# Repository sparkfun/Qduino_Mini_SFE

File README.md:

Qduino Mini
========================================

[*Qduino Mini - Arduino Dev Board (DEV-13614)*](https://www.sparkfun.com/products/13614)

The Qduino Mini is *perfect* to embed in your electronics projects, it's super small, inexpensive, has a battery connector & charger built-in, & a fuel gauge that can tell you when to charge the battery!

The **Qduino Mini is Arduino-compatible & 100% open source, hardware and software** meaning that making and programming your first circuit is a breeze.  Hardware is hard, so we decided to make it a little bit easier.  All of the design files, including EAGLE board files, schematic, and code have been released under an open source license.  Here's what it includes:

* **Battery Charger Circuit** - just plug in USB and it charges the battery with the auto switching circuit - there's no extra charger needed & no digging the battery out of your project so you can charge & program at the same time over USB!
* **Battery Fuel Gauge** - guessing on when your project runs out of juice?  We've got you covered - we have a simple monitor library for your battery so you can remind yourself when it needs a little extra juice.
* **Ultra small, Ultra thin, Ultra light** - The Qduino Mini itself is 0.8in x 1.5in (2cm x 3.9cm) & 0.18oz (5 grams), perfect for quadcopters, drones or high altitude balloon projects.  Both the Qduino Mini and the batteries (LiPos) used to power the board fit are super compact & thin, just right for embedding in your projects.

<h4>Tech Specs:</h4>

* **ATmega32U4 Processor** - Arduino Leonardo Compatible
* 32KB Flash Storage
* 2.5KB SRAM
* 1KB EEPROM
* 3.3V @ 8MHz
* 20 Digital I/O // 14 Dedicated
* 12 Analog Channels // 6 Dedicated
* 7 Digital I/O also PWM channels
* SPI, I2C, UART available
* Two RGB LEDs built-in - one for: Charge Status, TX, RX, and the * other user programmable
* **TPS78233** 3.3V 150mA Regulator
* **MCP73832** LiPo Battery Charger
* **MAX17048** LiPo Battery Fuel Gauge

The Qduino Mini is 100% made in the USA! Every board is made and quality tested at SparkFun Electronics, in Niwot, CO.

Documentation
--------------
* **[Introducing the Qduino Mini!](https://www.sparkfun.com/news/1754)** 
* **[Hookup Guide](https://www.hackster.io/team-qtechknow/qduino-mini-quickstart-guide-8b2d68)** - Basic hookup guide
* **[Hackster.io: Projects](https://www.hackster.io/qtechknow)** - Projects using the Qduino.
* **SparkFun: Projects**
  * **[DIY Light Sculpture](https://learn.sparkfun.com/tutorials/diy-light-sculpture)**
  * **[DIY Light-Up Shoes](https://learn.sparkfun.com/tutorials/diy-light-up-shoes)**
* **[SparkFun Arduino Board Add-on](https://github.com/sparkfun/Arduino_Boards)** - Board Add-on for the Qduino Mini
* **[SparkFun Fritzing Part](https://github.com/sparkfun/Fritzing_Parts/blob/main/products/13614_sfe_qtechknow_qduino_mini_arduino_development_board.fzpz)** - Fritzing diagrams for SparkFun products.
* **[SparkFun Graphical Datasheets](https://github.com/sparkfun/Graphical_Datasheets/tree/master/Datasheets/Qduino)** - Graphical Datasheets for various SparkFun products.

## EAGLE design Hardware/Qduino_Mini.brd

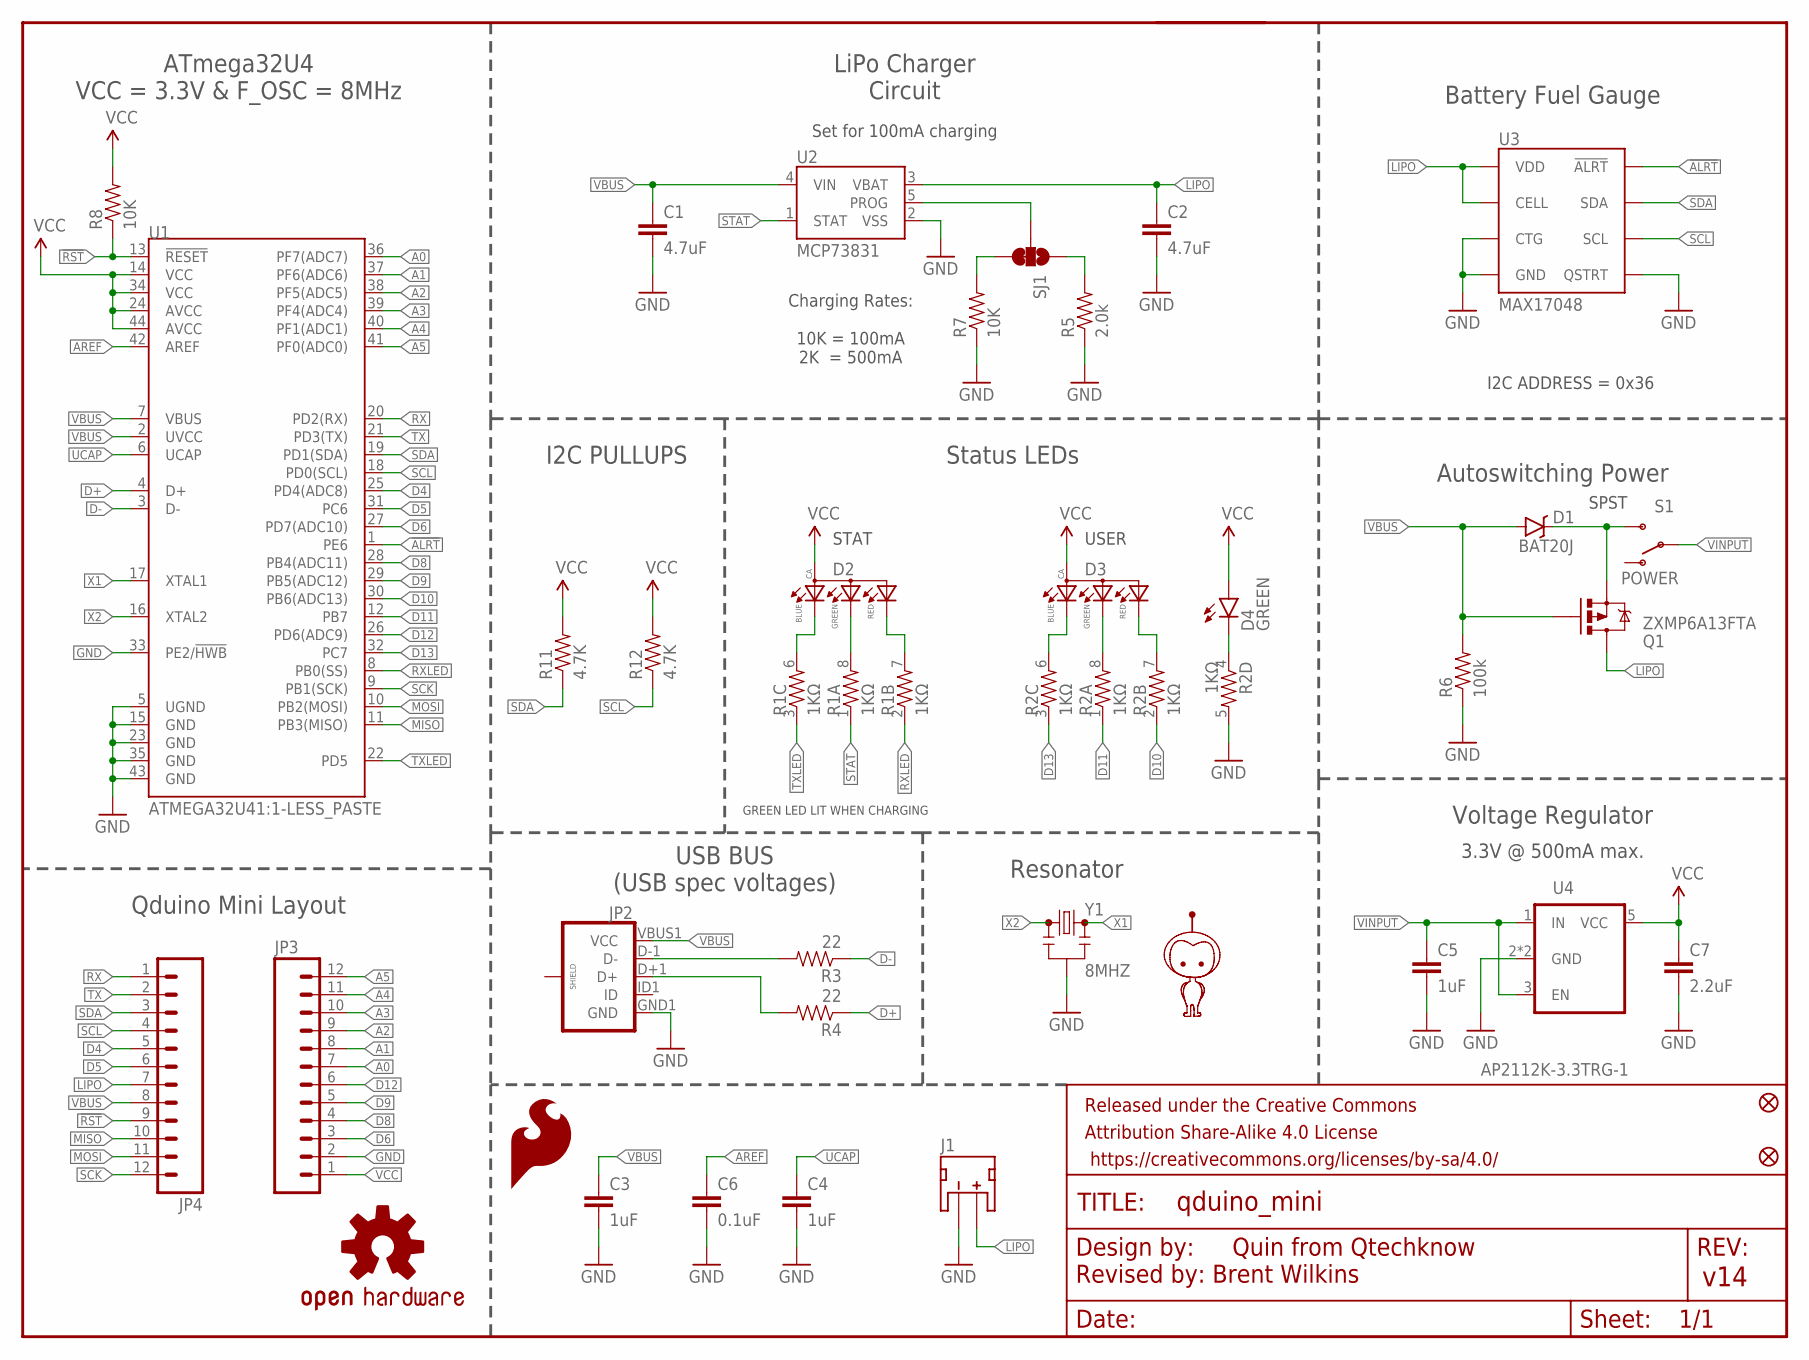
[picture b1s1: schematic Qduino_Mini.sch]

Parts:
C1, C2: 4.7uF; 0603-CAP
C3, C4, C5: 1uF; 0603-CAP
C6: 0.1uF; 0603-CAP
C7: 2.2uF; 0603-CAP
D1: BAT20J; SOD-323
D2, D3: 0.13_RGB_LEDPLCC; P-LCC-4-3
D4: GREEN; LED-0603
FID1, FID2: FIDUCIALUFIDUCIAL; MICRO-FIDUCIAL
FRAME2: FRAME-LETTER; CREATIVE_COMMONS
J1: LiPo; JST-2-SMD
JP2: USB_MICROB_PLUGCONN-11752; USB-B-MICRO-SMD_V03
JP3, JP4: M12PTH; 1X12
LOGO1: OSHW-LOGOS; OSHW-LOGO-S
LOGO2: SFE_LOGO_FLAME.1_INCH; SFE_LOGO_FLAME_.1
Q1: ZXMP6A13FTA; SOT23-3
R1, R2: 1KΩ; 0603-ARV
R3, R4: 22; 0603-RES
R5: 2.0k; 0603-RES
R6: 100k; 0603-RES
R7, R8: 10K; 0603-RES
R11, R12: 4.7K; 0603-RES
S1: POWER; SWITCH-SPST-SMD-A
SJ1: JUMPER-PAD-3-2OF3_NC_BY_TRACE_SMALL; PAD-JUMPER-3-2OF3_NC_BY_TRACE_YES_SILK_FULL_BOX
U1: ATMEGA32U41:1-LESS_PASTE; QFN-44-NOPAD_1:1-LESS_PASTE
U2: MCP73831; SOT23-5
U3: MAX17048; DFN-8
U4: AP2112K-3.3TRG-1; SOT23-5
U5: MIGHTYQ-L-SILK; LOGO-LARGE-SILK
Y1: 8MHZ; RESONATOR-SMD

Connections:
!ALRT: U1.1 (PE6), U3.P$5 (!ALRT)
!RST: JP4.9, R8.1, U1.13 (!RESET)
A0: JP3.7, U1.36 (PF7(ADC7))
A1: JP3.8, U1.37 (PF6(ADC6))
A2: JP3.9, U1.38 (PF5(ADC5))
A3: JP3.10, U1.39 (PF4(ADC4))
A4: JP3.11, U1.40 (PF1(ADC1))
A5: JP3.12, U1.41 (PF0(ADC0))
AREF: C6.1, U1.42 (AREF)
D4: JP4.5, U1.25 (PD4(ADC8))
D5: JP4.6, U1.31 (PC6)
D6: JP3.3, U1.27 (PD7(ADC10))
D8: JP3.4, U1.28 (PB4(ADC11))
D9: JP3.5, U1.29 (PB5(ADC12))
D10: R2.2 (1), U1.30 (PB6(ADC13))
D11: R2.1, U1.12 (PB7)
D12: JP3.6, U1.26 (PD6(ADC9))
D13: R2.3 (1), U1.32 (PC7)
D+: R4.1, U1.4 (D+)
D-: R3.1, U1.3 (D-)
GND: C1.2, C2.2, C3.2, C4.2, C5.2, C6.2, C7.2, J1.1 (-), JP2.GND1 (GND), JP3.2, R2.5 (2), R5.1, R6.1, R7.1, U1.5 (UGND), U1.15 (GND), U1.23 (GND), U1.33 (PE2/!HWB), U1.35 (GND), U1.43 (GND), U2.2 (VSS), U3.P$1 (CTG), U3.P$4 (GND), U3.P$6 (QSTRT), U3.P$9 (GND), U4.2 (GND), U4.4 (GND), Y1.2
INMOSFET: D1.C, Q1.2 (S), S1.3 (S)
LIPO: C2.1, J1.2 (+), JP4.7, Q1.3 (D), U2.3 (VBAT), U3.P$2 (CELL), U3.P$3 (VDD)
MISO: JP4.10, U1.11 (PB3(MISO))
MOSI: JP4.11, U1.10 (PB2(MOSI))
unnamed: D2.3 (BLUE), R1.6 (2)
unnamed: D2.2 (GREEN), R1.8 (2)
unnamed: D3.3 (BLUE), R2.6 (2)
unnamed: D4.C, R2.4 (1)
unnamed: R7.2, SJ1.3
unnamed: R5.2, SJ1.1
unnamed: D3.2 (GREEN), R2.8 (2)
unnamed: D2.1 (RED), R1.7 (2)
unnamed: D3.1 (RED), R2.7 (2)
PROG: SJ1.2, U2.5 (PROG)
RX: JP4.1, U1.20 (PD2(RX))
RXLED: R1.2 (1), U1.8 (PB0(SS))
SCK: JP4.12, U1.9 (PB1(SCK))
SCL: JP4.4, R12.1, U1.18 (PD0(SCL)), U3.P$7 (SCL)
SDA: JP4.3, R11.1, U1.19 (PD1(SDA)), U3.P$8 (SDA)
STAT: R1.1, U2.1 (STAT)
TX: JP4.2, U1.21 (PD3(TX))
TXLED: R1.3 (1), U1.22 (PD5)
UCAP: C4.1, U1.6 (UCAP)
UD+: JP2.D+1 (D+), R4.2
UD-: JP2.D-1 (D-), R3.2
VBUS: C1.1, C3.1, D1.A, JP2.VBUS1 (VCC), JP4.8, Q1.1 (G), R6.2, U1.2 (UVCC), U1.7 (VBUS), U2.4 (VIN)
VCC: C7.1, D2.4 (ANODE), D3.4 (ANODE), D4.A, JP3.1, R8.2, R11.2, R12.2, U1.14 (VCC), U1.24 (AVCC), U1.34 (VCC), U1.44 (AVCC), U4.5 (VCC)
VINPUT: C5.1, S1.2, U4.1 (IN), U4.3 (EN)
X1: U1.17 (XTAL1), Y1.3
X2: U1.16 (XTAL2), Y1.1

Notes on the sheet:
Set for 100mA charging
USB BUS (USB spec voltages)
Resonator
Status LEDs
3.3V @ 500mA max.
SPST
ATmega32U4 VCC = 3.3V & F_OSC = 8MHz
Qduino Mini Layout
LiPo Charger Circuit
Battery Fuel Gauge
Voltage Regulator
Autoswitching Power
Charging Rates: 10K = 100mA 2K = 500mA
I2C PULLUPS
Revised by: Brent Wilkins
I2C ADDRESS = 0x36
USER
STAT
GREEN LED LIT WHEN CHARGING

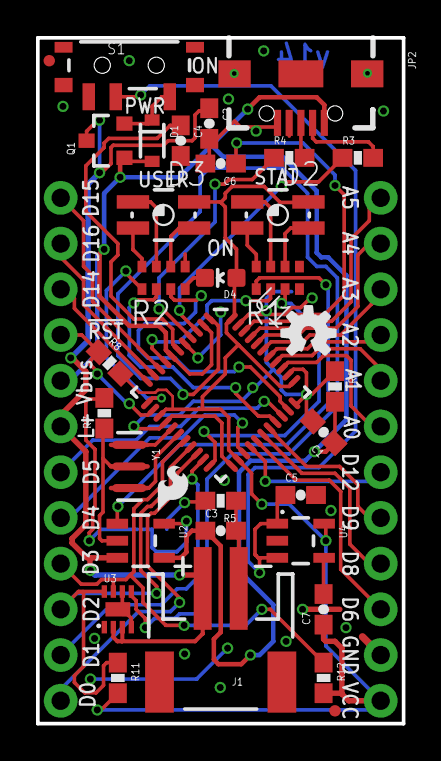
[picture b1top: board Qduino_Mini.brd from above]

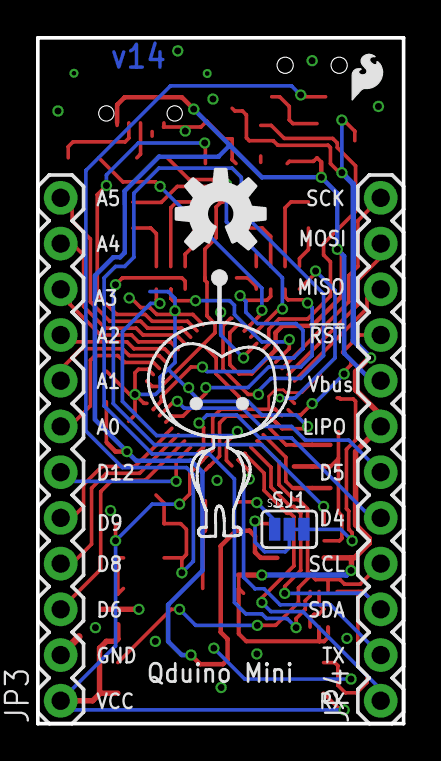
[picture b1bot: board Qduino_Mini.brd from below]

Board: 2 copper layers, 20.3 x 38.1 mm, 41 parts (6 on the bottom side), 51 nets.

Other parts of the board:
LOGO3: SFE_LOGO_FLAME.1_INCH; SFE_LOGO_FLAME_.1@1
U$4: OSHW-LOGO-M@1

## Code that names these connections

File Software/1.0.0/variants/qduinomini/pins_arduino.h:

/*
  pins_arduino.h - Pin definition functions for Arduino
  Part of Arduino - http://www.arduino.cc/

  Copyright (c) 2007 David A. Mellis

  This library is free software; you can redistribute it and/or
  modify it under the terms of the GNU Lesser General Public
  License as published by the Free Software Foundation; either
  version 2.1 of the License, or (at your option) any later version.

  This library is distributed in the hope that it will be useful,
  but WITHOUT ANY WARRANTY; without even the implied warranty of
  MERCHANTABILITY or FITNESS FOR A PARTICULAR PURPOSE.  See the GNU
  Lesser General Public License for more details.

  You should have received a copy of the GNU Lesser General
  Public License along with this library; if not, write to the
  Free Software Foundation, Inc., 59 Temple Place, Suite 330,
  Boston, MA  02111-1307  USA

  $Id: wiring.h 249 2007-02-03 16:52:51Z mellis $
*/

#ifndef Pins_Arduino_h
#define Pins_Arduino_h

#include <avr/pgmspace.h>

#define TX_RX_LED_INIT	DDRD |= (1<<5), DDRB |= (1<<0)
#define TXLED0			PORTD |= (1<<5)
#define TXLED1			PORTD &= ~(1<<5)
#define RXLED0			PORTB |= (1<<0)
#define RXLED1			PORTB &= ~(1<<0)

static const uint8_t SDA = 2;
static const uint8_t SCL = 3;

// Map SPI port to 'new' pins D14..D17
static const uint8_t SS   = 17;
static const uint8_t MOSI = 16;
static const uint8_t MISO = 14;
static const uint8_t SCK  = 15;

// Mapping of analog pins as digital I/O
// A6-A11 share with digital pins
static const uint8_t A0 = 18;
static const uint8_t A1 = 19;
static const uint8_t A2 = 20;
static const uint8_t A3 = 21;
static const uint8_t A4 = 22;
static const uint8_t A5 = 23;
static const uint8_t A6 = 24;	// D4
static const uint8_t A7 = 25;	// D6
static const uint8_t A8 = 26;	// D8
static const uint8_t A9 = 27;	// D9
static const uint8_t A10 = 28;	// D10
static const uint8_t A11 = 29;	// D12

#define digitalPinToPCICR(p)    ((((p) >= 8 && (p) <= 11) || ((p) >= 14 && (p) <= 17) || ((p) >= A8 && (p) <= A10)) ? (&PCICR) : ((uint8_t *)0))
#define digitalPinToPCICRbit(p) 0
#define digitalPinToPCMSK(p)    ((((p) >= 8 && (p) <= 11) || ((p) >= 14 && (p) <= 17) || ((p) >= A8 && (p) <= A10)) ? (&PCMSK0) : ((uint8_t *)0))
#define digitalPinToPCMSKbit(p) ( ((p) >= 8 && (p) <= 11) ? (p) - 4 : ((p) == 14 ? 3 : ((p) == 15 ? 1 : ((p) == 16 ? 2 : ((p) == 17 ? 0 : (p - A8 + 4))))))

//	__AVR_ATmega32U4__ has an unusual mapping of pins to channels
extern const uint8_t PROGMEM analog_pin_to_channel_PGM[];
#define analogPinToChannel(P)  ( pgm_read_byte( analog_pin_to_channel_PGM + (P) ) )

#ifdef ARDUINO_MAIN

// On the Arduino board, digital pins are also used
// for the analog output (software PWM).  Analog input
// pins are a separate set.

// ATMEL ATMEGA32U4 / ARDUINO LEONARDO
//
// D0           PD2   RXD1/INT2
// D1           PD3   TXD1/INT3
// D2           PD1   SDA       SDA/INT1
// D3#          PD0   PWM8/SCL  OC0B/SCL/INT0
// D4     A6    PD4   ADC8
// D5#          PC6   ???       OC3A/#OC4A
// D6#    A7    PD7   FastPWM   #OC4D/ADC10
// D7           PE6   INT6/AIN0
//
// D8     A8    PB4   ADC11/PCINT4
// D9#    A9		PB5   PWM16     OC1A/#OC4B/ADC12/PCINT5
// D10#   A10		PB6   PWM16     OC1B/0c4B/ADC13/PCINT6
// D11#         PB7   PWM8/16   0C0A/OC1C/#RTS/PCINT7
// D12    A11   PD6             T1/#OC4D/ADC9
// D13#         PC7   PWM10     CLK0/OC4A
//
// A0		  D18		PF7	  ADC7
// A1		  D19		PF6   ADC6
// A2		  D20 	PF5   ADC5
// A3		  D21 	PF4   ADC4
// A4     D22   PF1   ADC1
// A5     D23   PF0   ADC0
//
// New pins D14..D17 to map SPI port to digital pins
//
// MISO   D14   PB3   MISO,PCINT3
// SCK    D15   PB1   SCK,PCINT1
// MOSI   D16   PB2   MOSI,PCINT2
// SS     D17   PB0   RXLED,SS/PCINT0
//
// TXLED  PD5
// RXLED  PB0
// HWB    PE2   HWB

// these arrays map port names (e.g. port B) to the
// appropriate addresses for various functions (e.g. reading
// and writing)
const uint16_t PROGMEM port_to_mode_PGM[] = {
	NOT_A_PORT,
	NOT_A_PORT,
	(uint16_t) &DDRB,
	(uint16_t) &DDRC,
	(uint16_t) &DDRD,
	(uint16_t) &DDRE,
	(uint16_t) &DDRF,
};

const uint16_t PROGMEM port_to_output_PGM[] = {
	NOT_A_PORT,
	NOT_A_PORT,
	(uint16_t) &PORTB,
	(uint16_t) &PORTC,
	(uint16_t) &PORTD,
	(uint16_t) &PORTE,
	(uint16_t) &PORTF,
};

const uint16_t PROGMEM port_to_input_PGM[] = {
	NOT_A_PORT,
	NOT_A_PORT,
	(uint16_t) &PINB,
	(uint16_t) &PINC,
	(uint16_t) &PIND,
	(uint16_t) &PINE,
	(uint16_t) &PINF,
};

const uint8_t PROGMEM digital_pin_to_port_PGM[30] = {
	PD, // D0 - PD2
	PD,	// D1 - PD3
	PD, // D2 - PD1
	PD,	// D3 - PD0
	PD,	// D4 - PD4
	PC, // D5 - PC6
	PD, // D6 - PD7
	PE, // D7 - PE6
	
	PB, // D8  - PB4
	PB,	// D9  - PB5
	PB, // D10 - PB6
	PB,	// D11 - PB7
	PD, // D12 - PD6
	PC, // D13 - PC7
	
	PB,	// D14 - MISO - PB3
	PB,	// D15 - SCK  - PB1
	PB,	// D16 - MOSI - PB2
	PB,	// D17 - SS   - PB0
	
	PF,	// D18 - A0 - PF7
	PF, // D19 - A1 - PF6
	PF, // D20 - A2 - PF5
	PF, // D21 - A3 - PF4
	PF, // D22 - A4 - PF1
	PF, // D23 - A5 - PF0
	
	PD, // D24 / D4 - A6 - PD4
	PD, // D25 / D6 - A7 - PD7
	PB, // D26 / D8 - A8 - PB4
	PB, // D27 / D9 - A9 - PB5
	PB, // D28 / D10 - A10 - PB6
	PD, // D29 / D12 - A11 - PD6
};

const uint8_t PROGMEM digital_pin_to_bit_mask_PGM[30] = {
	_BV(2), // D0 - PD2
	_BV(3),	// D1 - PD3
	_BV(1), // D2 - PD1
	_BV(0),	// D3 - PD0
	_BV(4),	// D4 - PD4
	_BV(6), // D5 - PC6
	_BV(7), // D6 - PD7
	_BV(6), // D7 - PE6
	
	_BV(4), // D8 - PB4
	_BV(5),	// D9 - PB5
	_BV(6), // D10 - PB6
	_BV(7),	// D11 - PB7
	_BV(6), // D12 - PD6
	_BV(7), // D13 - PC7
	
	_BV(3),	// D14 - MISO - PB3
	_BV(1),	// D15 - SCK - PB1
	_BV(2),	// D16 - MOSI - PB2
	_BV(0),	// D17 - SS - PB0
	
	_BV(7),	// D18 - A0 - PF7
	_BV(6), // D19 - A1 - PF6
	_BV(5), // D20 - A2 - PF5
	_BV(4), // D21 - A3 - PF4
	_BV(1), // D22 - A4 - PF1
	_BV(0), // D23 - A5 - PF0
	
	_BV(4), // D24 / D4 - A6 - PD4
	_BV(7), // D25 / D6 - A7 - PD7
	_BV(4), // D26 / D8 - A8 - PB4
	_BV(5), // D27 / D9 - A9 - PB5
	_BV(6), // D28 / D10 - A10 - PB6
	_BV(6), // D29 / D12 - A11 - PD6
};

const uint8_t PROGMEM digital_pin_to_timer_PGM[16] = {
	NOT_ON_TIMER,	
	NOT_ON_TIMER,
	NOT_ON_TIMER,
	TIMER0B,		/* 3 */
	NOT_ON_TIMER,
	TIMER3A,		/* 5 */
	TIMER4D,		/* 6 */
	NOT_ON_TIMER,	
	
	NOT_ON_TIMER,	
	TIMER1A,		/* 9 */
	TIMER1B,		/* 10 */
	TIMER0A,		/* 11 */
	
	NOT_ON_TIMER,	
	TIMER4A,		/* 13 */
	
	NOT_ON_TIMER,	
	NOT_ON_TIMER,
};

const uint8_t PROGMEM analog_pin_to_channel_PGM[12] = {
	7,	// A0       PF7   ADC7
	6,	// A1       PF6   ADC6	
	5,	// A2       PF5   ADC5	
	4,	// A3       PF4   ADC4
	1,	// A4       PF1   ADC1	
	0,	// A5       PF0   ADC0	
	8,	// A6   D4  PD4   ADC8
	10,	// A7   D6  PD7   ADC10
	11,	// A8   D8  PB4   ADC11
	12,	// A9   D9  PB5   ADC12
	13,	// A10  D10 PB6   ADC13
	9	  // A11  D12 PD6   ADC9
};

#endif /* ARDUINO_MAIN */
#endif /* Pins_Arduino_h */

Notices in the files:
parts and their libraries:
SparkFun-Passives: Licensing: CC v3.0 Share-Alike You are welcome to use this library for commercial purposes.
SparkFun-Aesthetics: Released under the Creative Commons Attribution Share-Alike 4.0 License
SparkFun-Aesthetics: https://creativecommons.org/licenses/by-sa/4.0
